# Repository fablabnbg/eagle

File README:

To use the Fablab Eagle Files:
- Clone this git reposetory
- Add the directorys ( Controll-Pannel -> options -> Directorys )
- Have Fun

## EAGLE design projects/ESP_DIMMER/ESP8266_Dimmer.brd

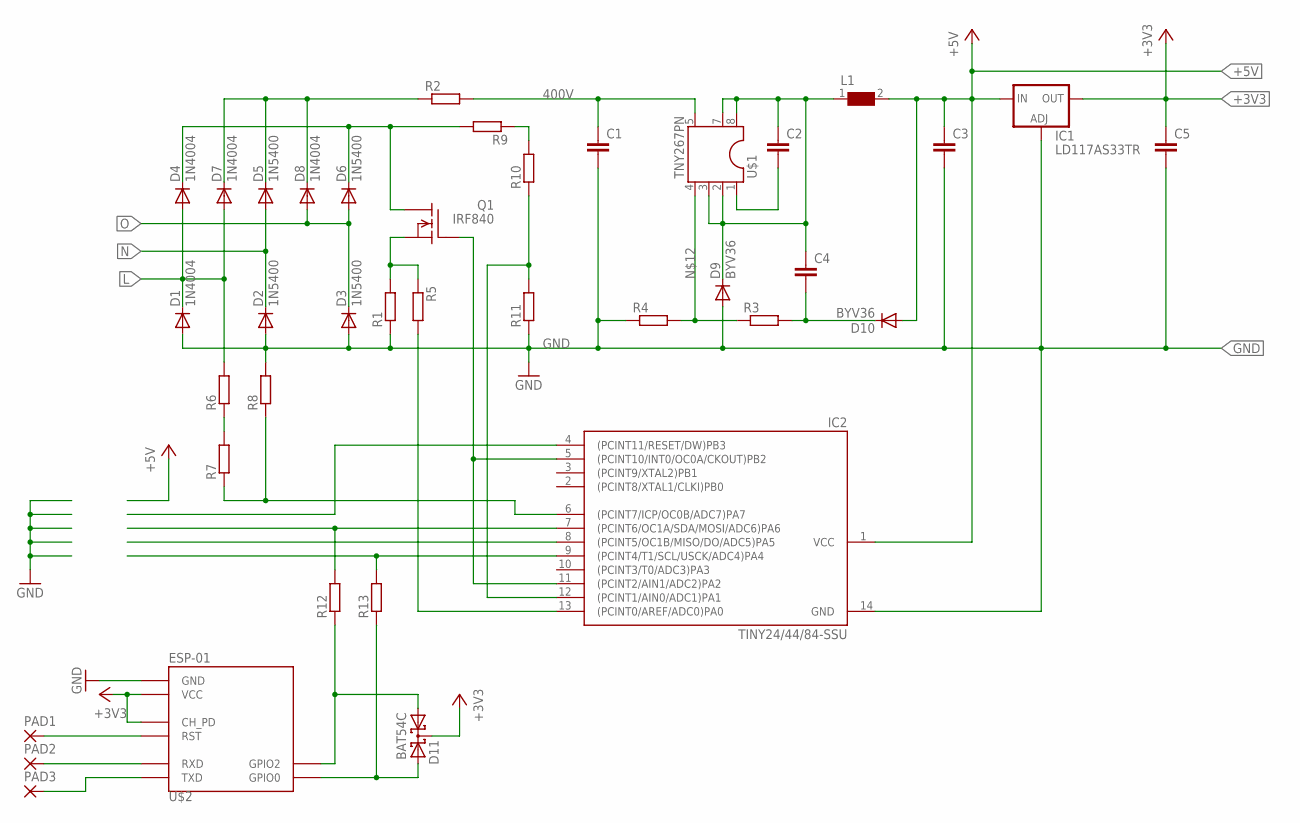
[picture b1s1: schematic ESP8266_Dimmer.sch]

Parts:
C1: C-EUC1812; C1812
C2, C3, C4, C5: C-EUC0805; C0805
D1, D4, D7, D8: 1N4004; DO41-10
D2, D3, D5, D6: 1N5400; DO201-15
D9, D10: BYV36; SOD57-10
D11: BAT54C; SOT23
IC1: LD117AS33TR; SOT223
IC2: TINY24/44/84-SSU; SOIC14
L1: WE-FPI; WE-FPI_744010...
PAD1, PAD2, PAD3: 1,6/0,8
Q1: IRF840; TO220
R1, R5: R-EU_M1206; M1206
R2: R-EU_0204/5; 0204/5
R3, R4: R-EU_R0805; R0805
R6, R7, R8, R9, R10, R11, R12, R13: R-EU_0204/7; 0204/7
U$1: TNY267PN; DIP-8B
U$2: ESP-01

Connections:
400V: C1.1, R2.2, U$1.5 (D)
+3V3: C5.1, D11.3 (CC), IC1.4 (OUT), U$2.CH_PD, U$2.VCC
+5V: C3.1, D10.A, IC1.3 (IN), IC2.1 (VCC), L1.2
GND: C1.2, C3.2, C5.2, D1.A, D2.A, D3.A, D9.A, IC1.1 (ADJ), IC2.14 (GND), R1.1, R4.1, R8.2, R11.1, U$2.GND
L: D1.C, D4.A, D7.A, R6.2
N: D2.C, D5.A
unnamed: IC2.13 ((PCINT0/AREF/ADC0)PA0), R5.2
unnamed: D4.C, D6.C, Q1.2 (D), R9.2
unnamed: D5.C, D7.C, D8.C, R2.1
unnamed: PAD1.1, U$2.RST
unnamed: C2.1, C4.1, D9.C, L1.1, U$1.2 (2GND), U$1.3 (3GND), U$1.7 (7HV-GND), U$1.8 (8HV-GND)
unnamed: Q1.3 (S), R1.2, R5.1
unnamed: C2.2, U$1.1 (BP)
unnamed: R6.1, R7.2
unnamed: IC2.6 ((PCINT7/ICP/OC0B/ADC7)PA7), R7.1, R8.1
unnamed: IC2.5 ((PCINT10/INT0/OC0A/CKOUT)PB2), IC2.11 ((PCINT2/AIN1/ADC2)PA2), Q1.1 (G)
unnamed: C4.2, D10.C, R3.2
unnamed: R3.1, R4.2, U$1.4 (EN/UV)
unnamed: R9.1, R10.2
unnamed: IC2.12 ((PCINT1/AIN0/ADC1)PA1), R10.1, R11.2
unnamed: IC2.9 ((PCINT4/T1/SCL/USCK/ADC4)PA4), R13.2
unnamed: IC2.7 ((PCINT6/OC1A/SDA/MOSI/ADC6)PA6), R12.2
unnamed: PAD2.1, U$2.RX (RXD)
unnamed: D11.1 (A1), R12.1, U$2.GPIO2
unnamed: D11.2 (A2), R13.1, U$2.GPIO0
unnamed: PAD3.1, U$2.TX (TXD)
O: D3.C, D6.A, D8.A

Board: 2 copper layers, 39 parts (0 on the bottom side), 27 nets, no tracks yet.

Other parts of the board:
U$3: PCB68

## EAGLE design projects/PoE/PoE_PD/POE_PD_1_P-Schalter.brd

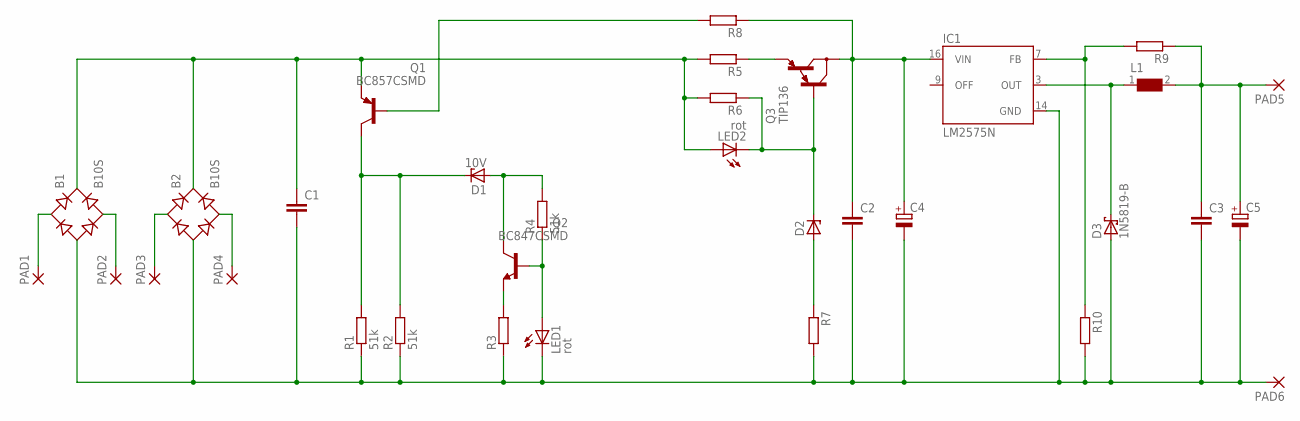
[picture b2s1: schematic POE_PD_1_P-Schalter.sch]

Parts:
B1, B2: B10S; MBS
C1, C2, C3: C-EUC0805; C0805
C4, C5: CPOL-EU153CLV-0807; 153CLV-0807
D1: 10V; SOT23
D2: ZENER-DIODESOT23; SOT23
D3: 1N5819-B; DO41-7.6
IC1: LM2575N; DIL16
L1: WE-PD2_S
LED1, LED2: rot; CHIP-LED0805
PAD1, PAD2, PAD3, PAD4, PAD5, PAD6: 2,15/1,0
Q1: BC857CSMD; SOT23-BEC
Q2: BC847CSMD; SOT23
Q3: TIP136; TO220
R1, R2, R4: 51k; R0603
R3, R5, R6, R7, R8, R9, R10: R-EU_R0603; R0603

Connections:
unnamed: B1.-, B2.-, C1.2, C2.2, C3.2, C4.-, C5.-, D3.A, IC1.14 (GND), LED1.C, PAD6.1, R1.1, R2.1, R3.1, R7.2, R10.2
unnamed: B1.+, B2.+, C1.1, LED2.A, Q1.E, R5.2, R6.2
unnamed: D1.3 (C), Q1.C, R1.2, R2.2
unnamed: LED1.A, Q2.1 (B), R4.1
unnamed: B1.AC1, PAD1.1
unnamed: Q2.2 (E), R3.2
unnamed: Q1.B, R8.2
unnamed: D1.1 (A), Q2.3 (C), R4.2
unnamed: D2.1 (A), R7.1
unnamed: Q3.3 (E), R5.1
unnamed: D2.3 (C), LED2.C, Q3.1 (B), R6.1
unnamed: D3.C, IC1.3 (OUT), L1.1
unnamed: C3.1, C5.+, L1.2, PAD5.1, R9.1
unnamed: C2.1, C4.+, IC1.16 (VIN), Q3.2 (C), R8.1
unnamed: IC1.7 (FB), R9.2, R10.1
unnamed: B1.AC2, PAD2.1
unnamed: B2.AC1, PAD3.1
unnamed: B2.AC2, PAD4.1

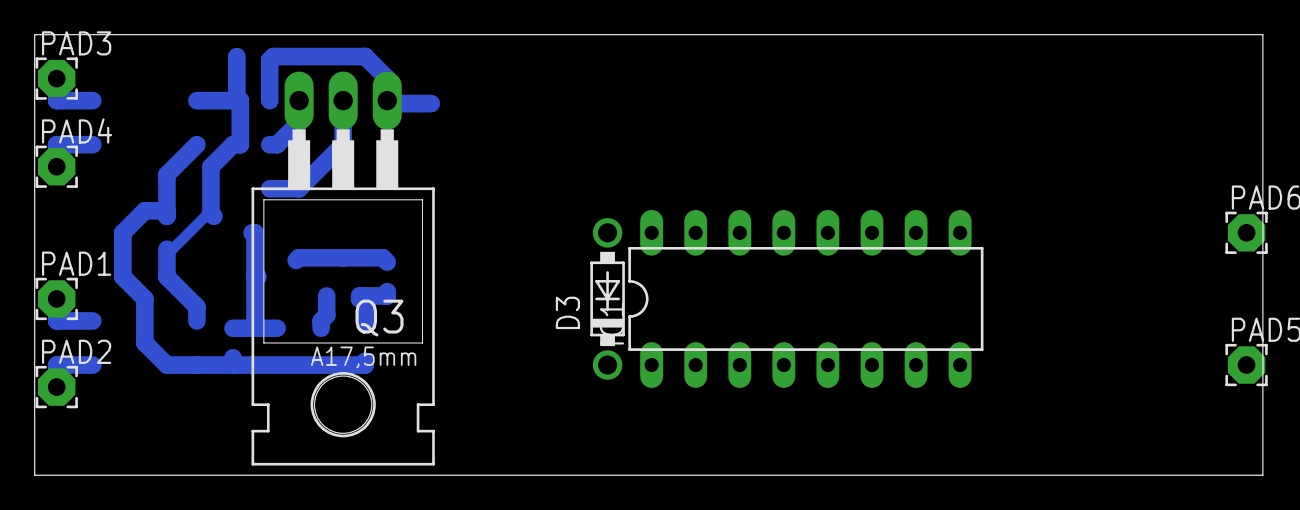
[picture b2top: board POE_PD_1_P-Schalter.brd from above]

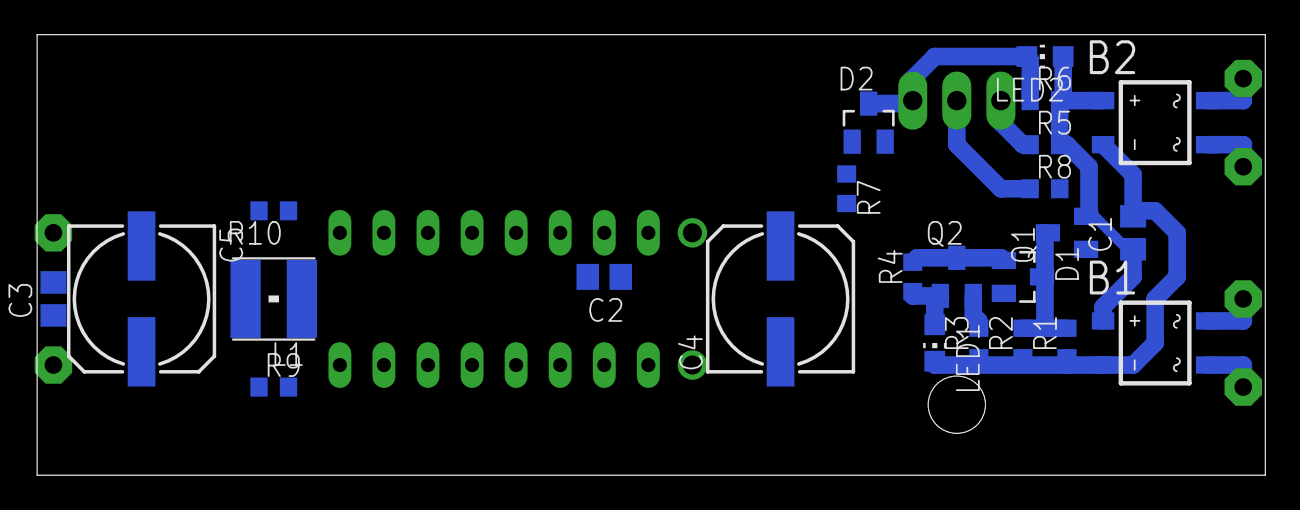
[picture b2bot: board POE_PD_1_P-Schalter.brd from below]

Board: 2 copper layers, 70.8 x 25.4 mm, 33 parts (24 on the bottom side), 18 nets.

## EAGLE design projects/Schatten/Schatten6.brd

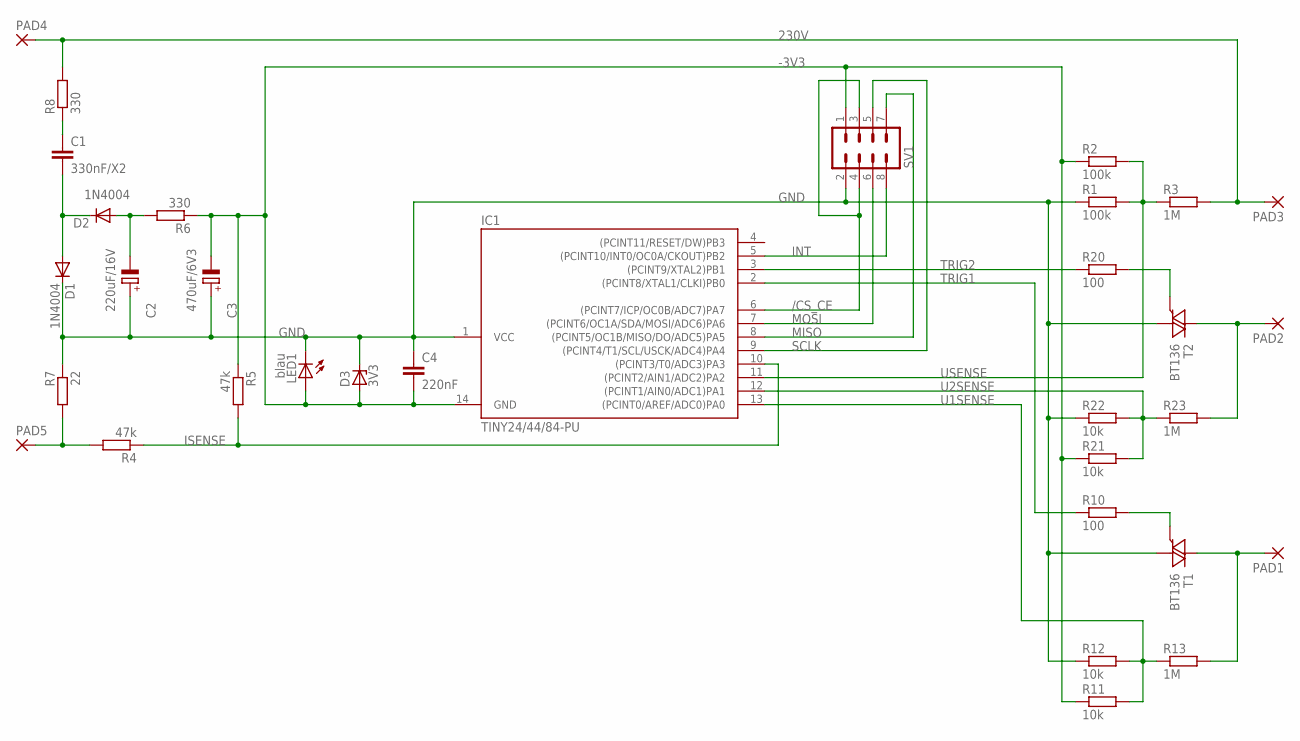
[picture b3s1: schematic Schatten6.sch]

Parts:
C1: 330nF/X2; C150-064X183
C2: 220uF/16V; E5-8,5
C3: 470uF/6V3; E5-8,5
C4: 220nF; C3225
D1, D2: 1N4004; DO41-10
D3: 3V3; ZDIO-7.5
IC1: TINY24/44/84-PU; DIL14
LED1: blau; LED3MM
PAD1, PAD2, PAD3, PAD4, PAD5: 1,6/0,9
R1, R2: 100k; 0207/10
R3, R13, R23: 1M; 0207/10
R4: 47k; 0207/10
R5: 47k; 0204V
R6, R8: 330; 0207/10
R7: 22; 0207/10
R10, R20: 100; 0207/10
R11: 10k; 0204/7
R12, R21, R22: 10k; 0207/10
SV1: MA04-2
T1, T2: BT136; TO220AB

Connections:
230V: PAD3.1, PAD4.1, R3.2, R8.2
-3V3: C3.-, C4.2, D3.A, IC1.14 (GND), LED1.A, R2.1, R5.1, R6.1, R11.1, R21.1, SV1.1
/CS_CE: IC1.6 ((PCINT7/ICP/OC0B/ADC7)PA7), SV1.3, SV1.4
GND: C2.+, C3.+, C4.1, D1.C, D3.C, IC1.1 (VCC), LED1.K (C), R1.1, R7.1, R12.1, R22.1, SV1.2, T1.1 (A1), T2.1 (A1)
INT: IC1.5 ((PCINT10/INT0/OC0A/CKOUT)PB2), SV1.8
ISENSE: IC1.10 ((PCINT3/T0/ADC3)PA3), R4.1, R5.2
MISO: IC1.8 ((PCINT5/OC1B/MISO/DO/ADC5)PA5), SV1.7
MOSI: IC1.7 ((PCINT6/OC1A/SDA/MOSI/ADC6)PA6), SV1.6
unnamed: PAD5.1, R4.2, R7.2
unnamed: PAD1.1, R13.2, T1.2 (A2)
unnamed: PAD2.1, R23.2, T2.2 (A2)
unnamed: R20.2, T2.3 (G)
unnamed: R10.2, T1.3 (G)
unnamed: C1.1, R8.1
unnamed: C1.2, D1.A, D2.C
unnamed: C2.-, D2.A, R6.2
SCLK: IC1.9 ((PCINT4/T1/SCL/USCK/ADC4)PA4), SV1.5
TRIG1: IC1.2 ((PCINT8/XTAL1/CLKI)PB0), R10.1
TRIG2: IC1.3 ((PCINT9/XTAL2)PB1), R20.1
U1SENSE: IC1.13 ((PCINT0/AREF/ADC0)PA0), R11.2, R12.2, R13.1
U2SENSE: IC1.12 ((PCINT1/AIN0/ADC1)PA1), R21.2, R22.2, R23.1
USENSE: IC1.11 ((PCINT2/AIN1/ADC2)PA2), R1.2, R2.2, R3.1

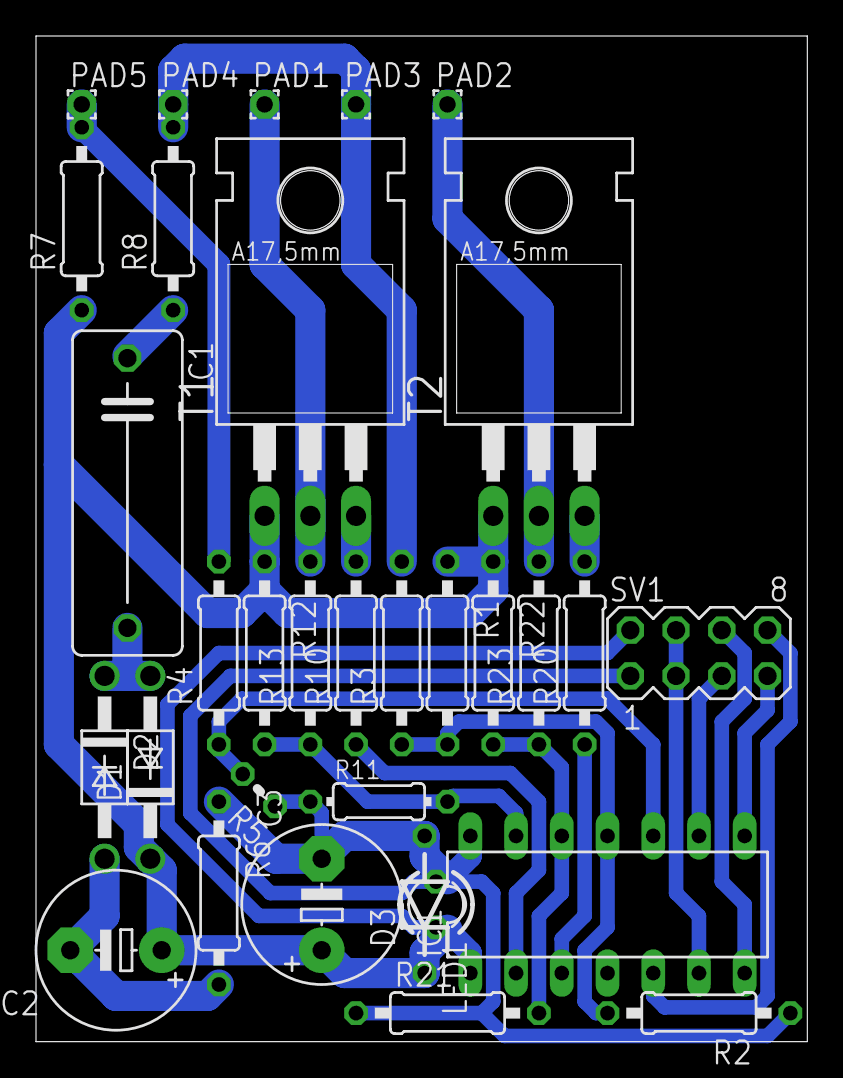
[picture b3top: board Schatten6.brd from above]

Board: 2 copper layers, 42.9 x 55.9 mm, 33 parts (1 on the bottom side), 22 nets.

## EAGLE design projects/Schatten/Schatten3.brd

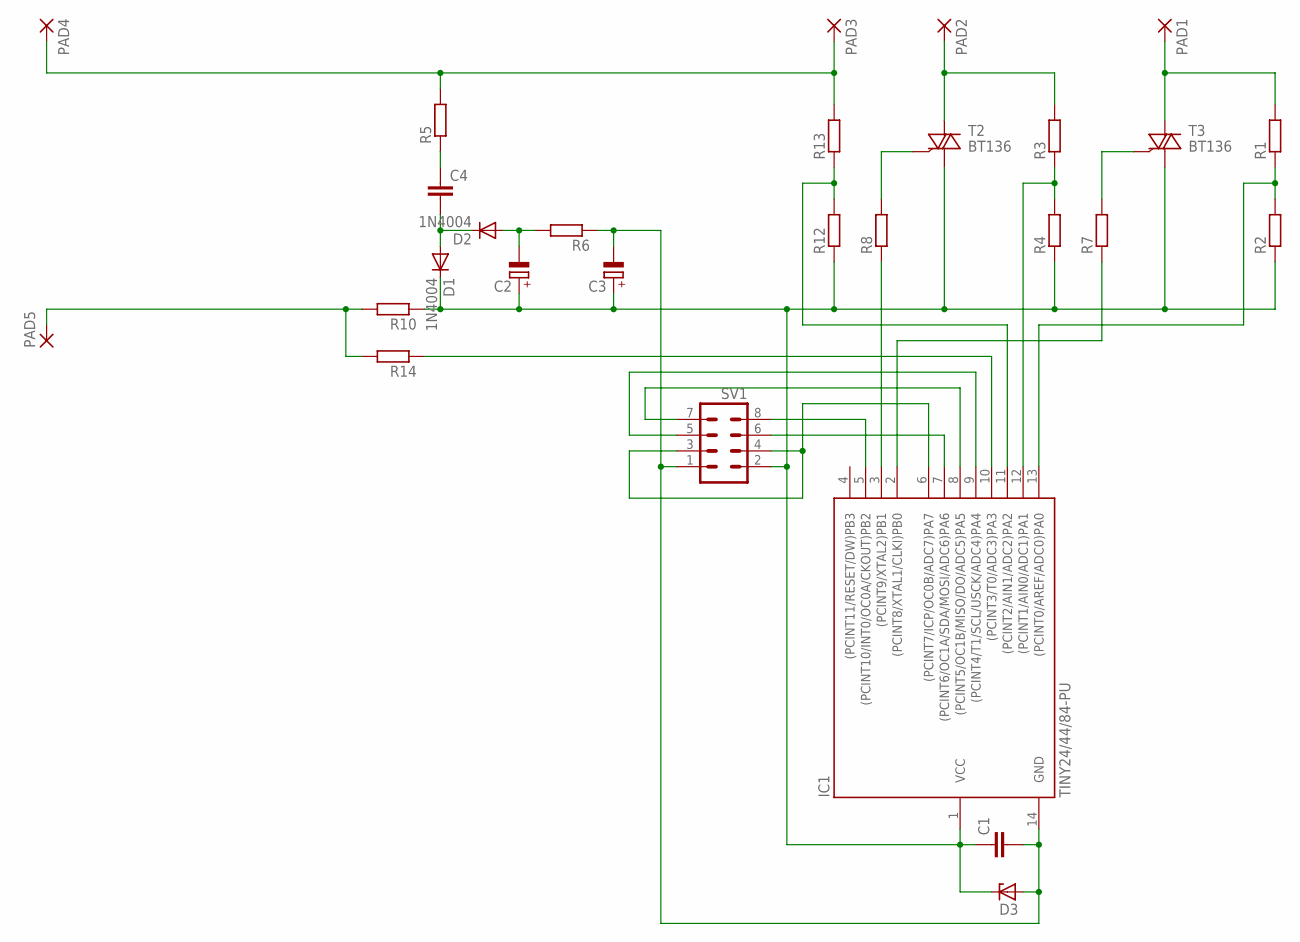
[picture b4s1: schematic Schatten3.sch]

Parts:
C1: C-EUC3225; C3225
C2, C3: CPOL-EUE5-8.5; E5-8,5
C4: C-EU150-064X183; C150-064X183
D1, D2: 1N4004; DO41-10
D3: ZENER-DIODEZD-7.5; ZDIO-7.5
IC1: TINY24/44/84-PU; DIL14
PAD1, PAD2, PAD3, PAD4, PAD5: 1,6/0,9
R1, R2, R3, R4, R5, R6, R7, R8, R10, R12, R13, R14: R-EU_0207/10; 0207/10
SV1: MA04-2
T2, T3: BT136; TO220AB

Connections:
unnamed: PAD5.1, R10.2, R14.2
unnamed: IC1.13 ((PCINT0/AREF/ADC0)PA0), R1.1, R2.2
unnamed: IC1.10 ((PCINT3/T0/ADC3)PA3), R14.1
unnamed: IC1.7 ((PCINT6/OC1A/SDA/MOSI/ADC6)PA6), SV1.6
unnamed: IC1.12 ((PCINT1/AIN0/ADC1)PA1), R3.1, R4.2
unnamed: IC1.2 ((PCINT8/XTAL1/CLKI)PB0), R7.1
unnamed: PAD1.1, R1.2, T3.2 (A2)
unnamed: PAD2.1, R3.2, T2.2 (A2)
unnamed: IC1.3 ((PCINT9/XTAL2)PB1), R8.1
unnamed: IC1.8 ((PCINT5/OC1B/MISO/DO/ADC5)PA5), SV1.7
unnamed: R8.2, T2.3 (G)
unnamed: R7.2, T3.3 (G)
unnamed: IC1.11 ((PCINT2/AIN1/ADC2)PA2), R12.2, R13.1
unnamed: IC1.9 ((PCINT4/T1/SCL/USCK/ADC4)PA4), SV1.5
unnamed: IC1.5 ((PCINT10/INT0/OC0A/CKOUT)PB2), SV1.8
unnamed: IC1.6 ((PCINT7/ICP/OC0B/ADC7)PA7), SV1.3, SV1.4
unnamed: PAD3.1, PAD4.1, R5.2, R13.2
unnamed: C1.1, C2.+, C3.+, D1.C, D3.C, IC1.1 (VCC), R2.1, R4.1, R10.1, R12.1, SV1.2, T2.1 (A1), T3.1 (A1)
unnamed: C4.1, R5.1
unnamed: C4.2, D1.A, D2.C
unnamed: C2.-, D2.A, R6.2
unnamed: C1.2, C3.-, D3.A, IC1.14 (GND), R6.1, SV1.1

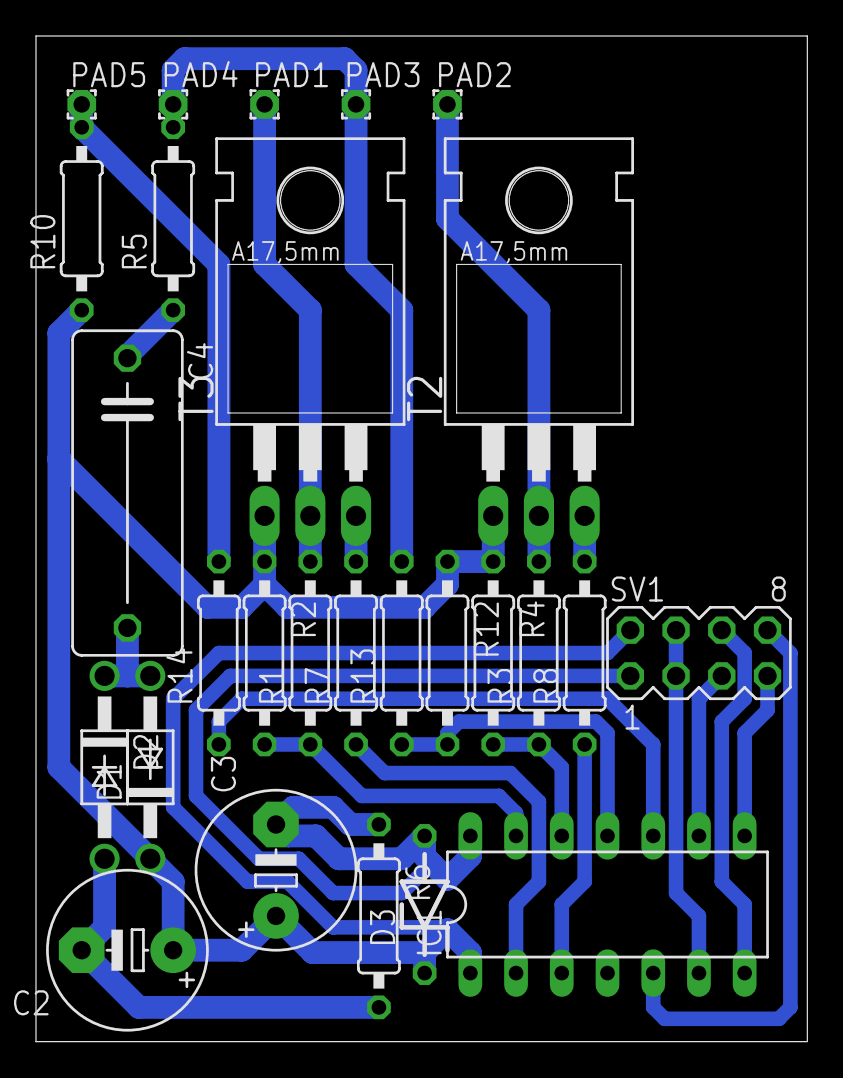
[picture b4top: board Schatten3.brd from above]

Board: 2 copper layers, 42.9 x 55.9 mm, 28 parts (1 on the bottom side), 22 nets.

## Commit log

2014-10-31 Added eagle directorys and some dummy Files
2014-11-09 Added .gitignore to avoid saving of eagle automatic Backups in git
2014-11-29 Cleaning up Schimmi's project-files and empty folders
2014-11-29 Small lib for some ABB fuse box parts
2014-11-29 Lib for Arietta G25
2014-11-29 Some pneumatic parts for fluid plans
2015-09-14 Removed unneeded file
2015-09-14 Added E233 hour counter to ABB library
2015-09-14 Copied male and female pin header libraries, as these always need some modifications (lesser than 5 pin headers etc.) Added 4 pin female header
2015-09-14 Created microchip library Added HCS301 rolling code chip in DIP and SOIC
2015-09-14 Mirrored explode.ulp from cadsoft site including credit file for the author
2017-04-01 Initial Design for ESP Dimmer Not checked Not routed Maybe single sided routable Not isolated
2017-04-01 Added pdf preview -Files
2017-04-03 Change wrong Diode after first Review

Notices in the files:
parts and their libraries:
wuerth_elektronik_EAGLE: Copyright: Würth Elektronik eiSos
